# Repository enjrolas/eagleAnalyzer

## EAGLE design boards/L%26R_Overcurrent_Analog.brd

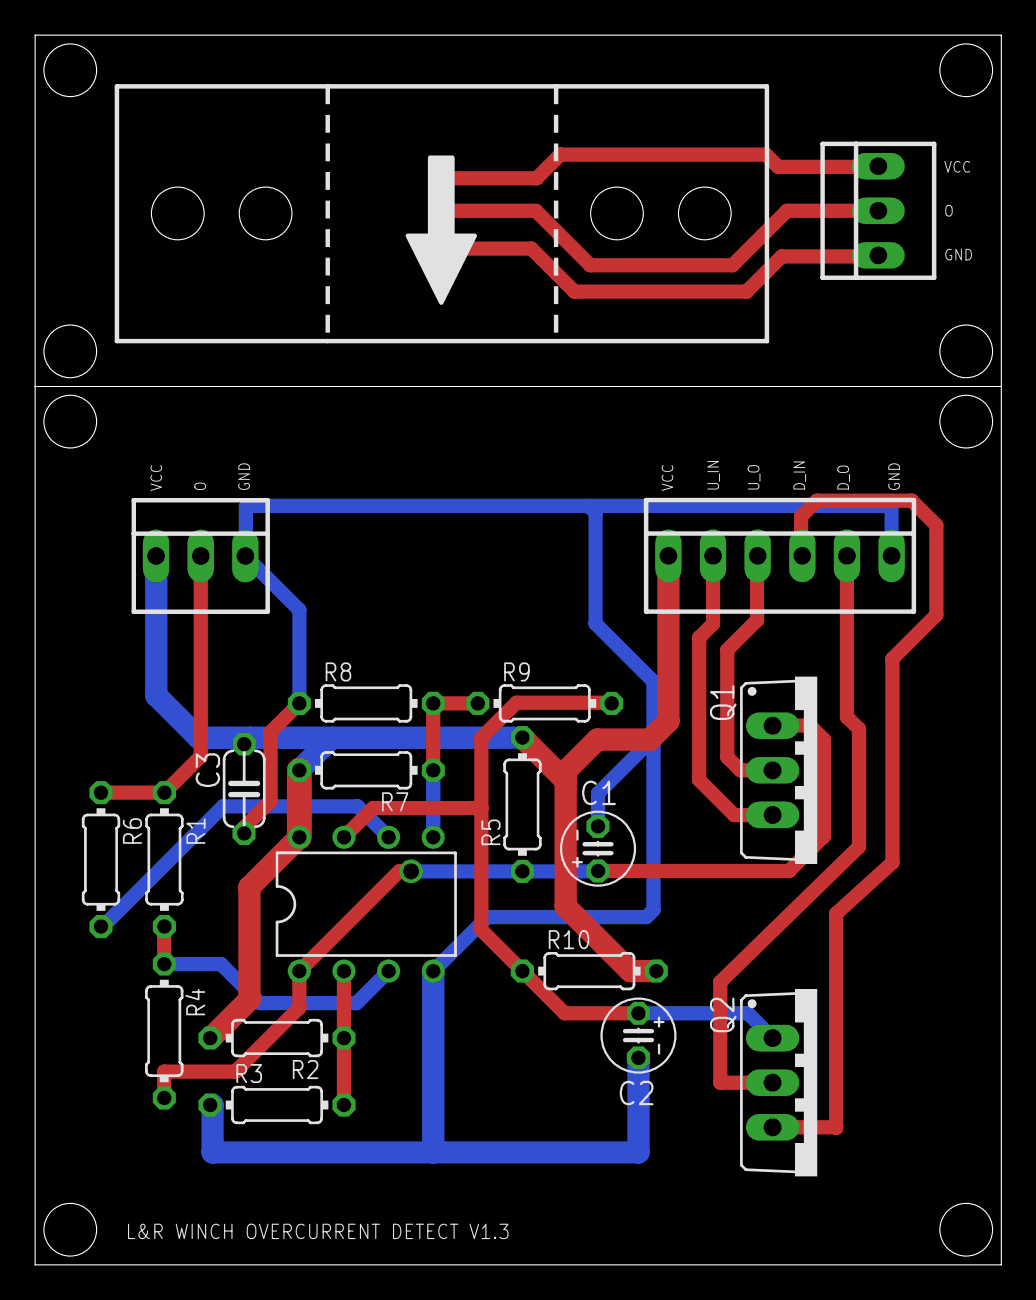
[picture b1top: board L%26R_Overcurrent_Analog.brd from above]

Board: 2 copper layers, 55.0 x 70.0 mm, 20 parts (0 on the bottom side), 16 nets.

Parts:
C1: 22u; C025-050X050
C2: 22u\; C025-050X050
C3: 0.1u; C050-024X044
IC1: CSLA2CFTH; CSLA2CF
IC2: TLC393CPN; DIL08
Q1, Q2: SUP75P0307; TO220BV
R1, R6: 3k; 0204/7
R2, R5, R10: 10k; 0204/7
R3: 24k; 0204/7
R4, R9: 1M; 0204/7
R7: 15k; 0204/7
R8: 6.2k; 0204/7
X1: J1; 22-23-2061
X2: J2; 22-23-2031
X3: J3; 22-23-2031

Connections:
+12V: C3.1, IC2.8, R2.2, R5.2, R7.2, R10.2, X1.1, X2.1
GND: C1.2, C2.2, C3.2, IC2.4, R3.1, R8.1, X1.6, X2.3
unnamed: IC2.3, R1.2, R4.1
unnamed: IC2.2, R2.1, R3.2
unnamed: IC2.6, R6.2
unnamed: IC2.5, R7.1, R8.2, R9.1
unnamed: C1.1, IC2.1, Q1.G, R4.2, R5.1
unnamed: C2.1, IC2.7, Q2.G, R9.2, R10.1
unnamed: Q1.S, X1.2
unnamed: Q1.D, X1.3
unnamed: Q2.S, X1.4
unnamed: Q2.D, X1.5
unnamed: IC1.V+, X3.1
unnamed: IC1.V-, X3.3
unnamed: IC1.O, X3.2
unnamed: R1.1, R6.1, X2.2

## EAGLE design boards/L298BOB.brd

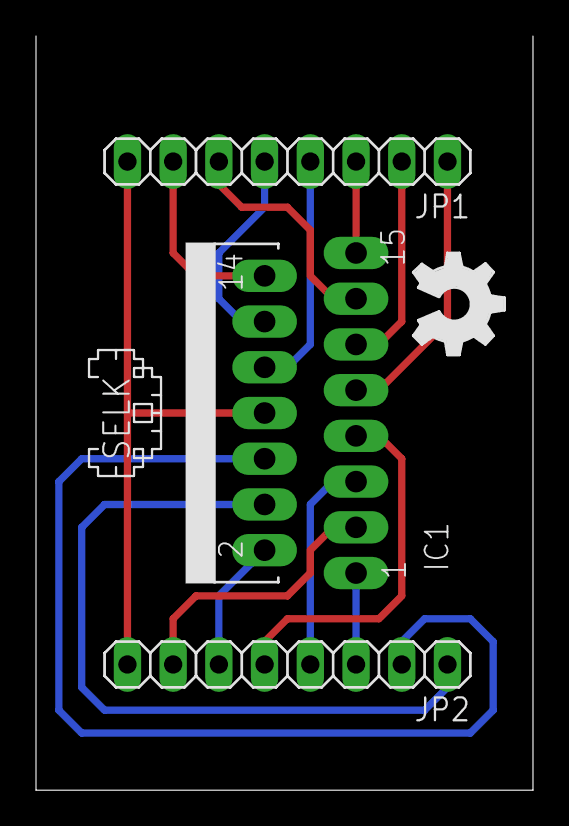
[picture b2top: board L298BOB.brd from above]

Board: 2 copper layers, 27.6 x 41.9 mm, 5 parts (0 on the bottom side), 15 nets.

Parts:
IC1: L298; MULTIWATT-15
JP1, JP2: 1X08
LOGO1: OSHW_LOGO_FILLX0200-NT; OSHW_FILLX200_NOTEXT
U$1: SELK02

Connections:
GND: IC1.8, JP1.8, JP2.8
unnamed: IC1.4, JP2.1
unnamed: IC1.1, JP2.3
unnamed: IC1.5, JP2.4
unnamed: IC1.7, JP2.5
unnamed: IC1.2, JP2.6
unnamed: IC1.3, JP2.7
unnamed: IC1.9, JP1.1
unnamed: IC1.6, JP2.2
unnamed: IC1.11, JP1.2
unnamed: IC1.15, JP1.3
unnamed: IC1.10, JP1.4
unnamed: IC1.12, JP1.5
unnamed: IC1.13, JP1.6
unnamed: IC1.14, JP1.7

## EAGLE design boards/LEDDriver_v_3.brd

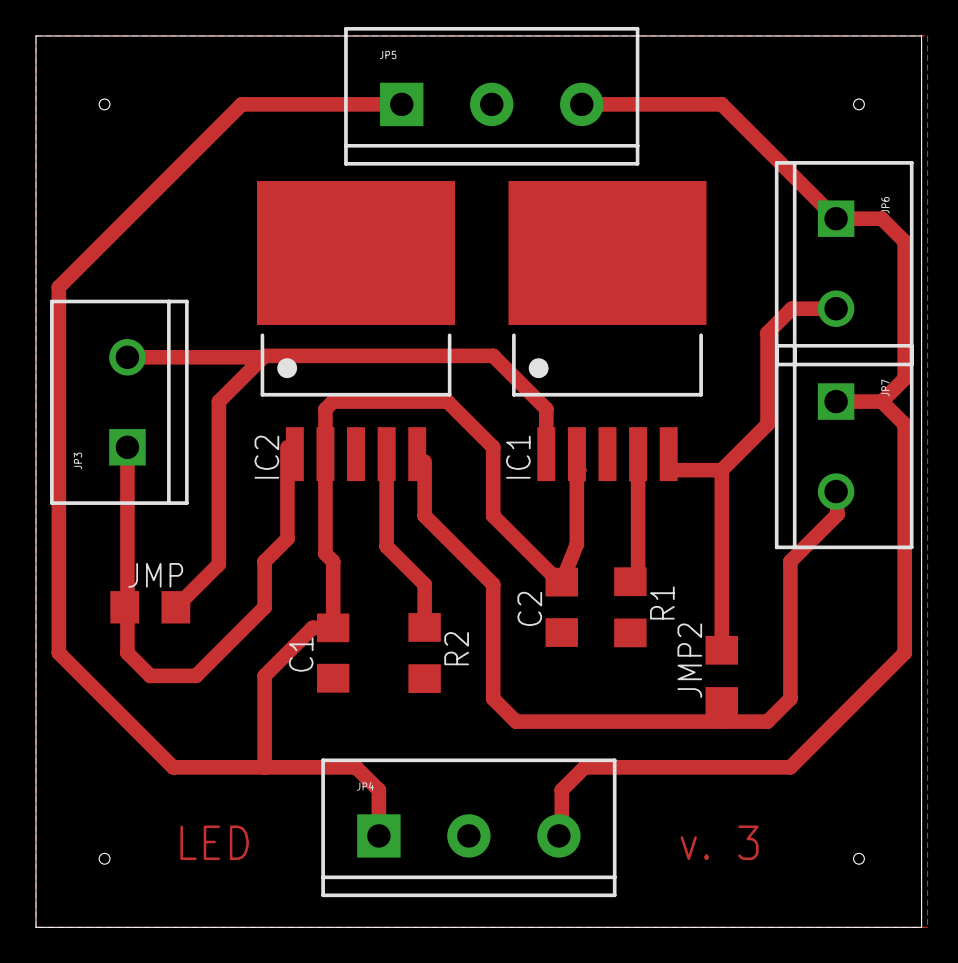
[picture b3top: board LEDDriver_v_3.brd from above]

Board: 2 copper layers, 49.2 x 49.5 mm, 13 parts (0 on the bottom side), 9 nets.

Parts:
C1, C2: C1206
IC1, IC2: CAT4101; TO263_5
JMP: CH; R1206
JMP2: AMP; R1206
JP3, JP6, JP7: M025MM; SCREWTERMINAL-5MM-2
JP4, JP5: SCREWTERMINAL-5MM-3
R1, R2: R1206

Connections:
+5V: C1.2, C2.2, IC1.2, IC2.2, JP4.1, JP5.1
+12V: JP4.3, JP5.3, JP6.1, JP7.1
GND: C1.1, C2.1, IC1.3, IC1.TAB, IC2.3, IC2.TAB, JP4.2, JP5.2, R1.2, R2.2
unnamed: IC1.1, JMP.2, JP3.2
unnamed: IC2.1, JMP.1, JP3.1
unnamed: IC1.4, R1.1
unnamed: IC2.5, JMP2.1, JP7.2
unnamed: IC1.5, JMP2.2, JP6.2
unnamed: IC2.4, R2.1

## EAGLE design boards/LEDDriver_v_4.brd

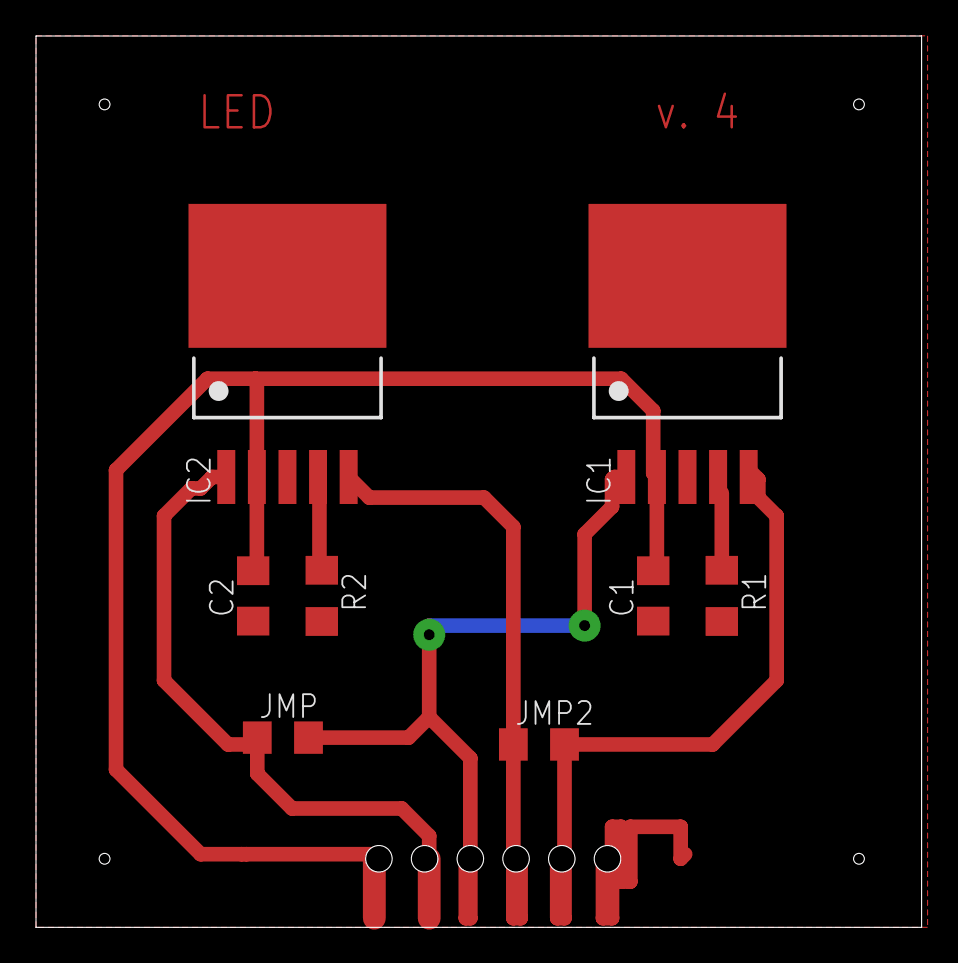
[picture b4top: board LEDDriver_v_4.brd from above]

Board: 2 copper layers, 49.2 x 49.5 mm, 9 parts (0 on the bottom side), 8 nets.

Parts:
C1, C2: C1206
IC1, IC2: CAT4101; TO263_5
JMP: CH; R1206
JMP2: AMP; R1206
JP1: 1X06_HOLES_ONLY
R1, R2: R1206

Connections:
+5V: C1.2, C2.2, IC1.2, IC2.2, JP1.6
GND: C1.1, C2.1, IC1.3, IC1.TAB, IC2.3, IC2.TAB, JP1.1, R1.2, R2.2
unnamed: IC1.1, JMP.2, JP1.4
unnamed: IC2.1, JMP.1, JP1.5
unnamed: IC1.4, R1.1
unnamed: IC2.5, JMP2.1, JP1.3
unnamed: IC1.5, JMP2.2, JP1.2
unnamed: IC2.4, R2.1

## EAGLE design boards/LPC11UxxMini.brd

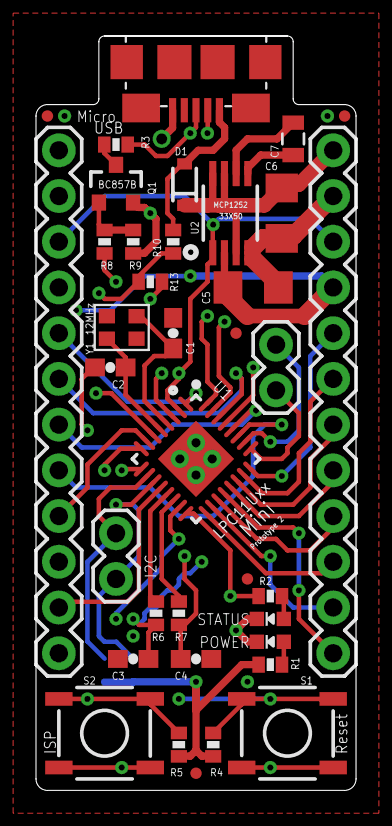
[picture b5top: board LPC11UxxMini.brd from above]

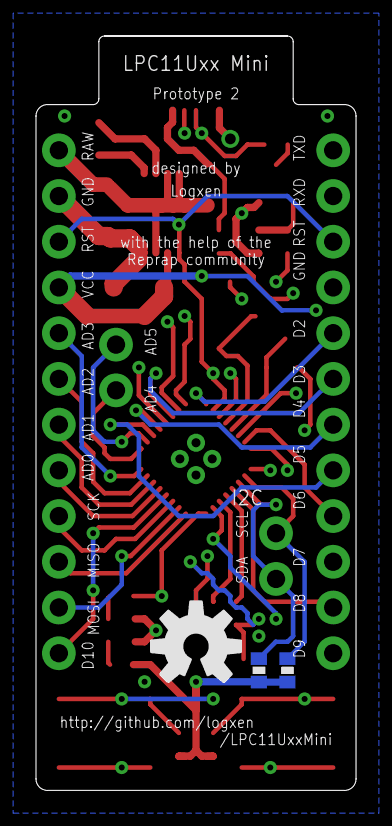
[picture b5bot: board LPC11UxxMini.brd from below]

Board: 4 copper layers, 17.8 x 41.9 mm, 40 parts (3 on the bottom side), 42 nets.

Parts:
C1, C2, C3, C4: 18pF; 0603-CAP
C5, C6: 10uF; 1206
C7: 1uF; 0805
D1: B0540WS-7; SOD-323
JP1, JP2: M12PTH; 1X12
JP3, JP6, JP7, JP8, JP9: FIDUCIALUFIDUCIAL; MICRO-FIDUCIAL
JP4: I2C; 1X02
JP5: ADC; 1X02
POWER: 20mA; CHIPLED_0603_NOOUTLINE
Q1: BC857B; SOT23-3
R1: 330 Ohm; 0402-RES
R2: 200 Ohm; 0402-RES
R3: 1.5kOhm; 0402-RES
R4, R5, R11, R12, R13: 10kOhm; 0402-RES
R6, R7: 33 Ohm; 0402-RES
R8: 3kOhm; 0402-RES
R9: 24kOhm; 0402-RES
R10: 100 Ohm; 0402-RES
S1: Reset; TACTILE_SWITCH_SMD
S2: ISP; TACTILE_SWITCH_SMD
STATUS: 20mA; CHIPLED_0603_NOOUTLINE
U1: LPC11Uxx; HVQFN32-5X5_3MMTHERMAL
U2: MCP1252-33X50I/MS; MSOP8_0.65MM
U$1: USB-MICROB-SMDRECEPT; USB-MICROB-RECEPT
U$4: OSHW-LOGO-M
Y1: 12MHz; CRYSTAL_2.5X2

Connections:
AD0: JP2.5, U1.21
AD1: JP2.6, U1.22
AD2: JP2.7, U1.23
AD3: JP2.8, U1.24
AD4: JP5.1, U1.25
AD5: JP5.2, U1.26
D2: JP1.5, U1.1
D3: JP1.6, U1.30
D4: JP1.7, U1.28
D5: JP1.8, U1.27
D6: JP1.9, U1.7
D7: JP1.10, U1.8
D8: JP1.11, U1.12
D9: JP1.12, R2.1, U1.16
D10: JP2.1, U1.20
GND: C1.2, C2.2, C3.2, C4.2, C5.2, C6.2, JP1.4, JP2.11, POWER.C, R13.1, S1.1, S1.2, S2.1, S2.2, STATUS.C, U1.THERMAL, U1.THERMAL@1, U1.THERMAL@2, U1.THERMAL@3, U1.THERMAL@4, U2.4, U$1.5
ISP: R5.1, S2.3, S2.4, U1.3
MC_USB_DM: R6.2, U1.13
MC_USB_DP: R7.2, U1.14
MC_USB_VBUS: R10.2, R13.2, U1.9
MISO: JP2.3, U1.17
MOSI: JP2.2, U1.18
POWER_LED_RESISTOR: POWER.A, R1.2
PWRREG_C+: C7.1, U2.6
PWRREG_C-: C7.2, U2.5
RST: JP1.3, JP2.10, R4.1, S1.3, S1.4, U1.2, U2.1
RXD: JP1.2, U1.31
SCK: JP2.4, U1.19
SCL: JP4.2, R11.1, U1.10
SDA: JP4.1, R12.1, U1.11
STATUS_LED_RESISTOR: R2.2, STATUS.A
TXD: JP1.1, U1.32
USB_CONNECT: R8.1, U1.15
USB_CONNECT_BASE: Q1.1, R8.2, R9.1
USB_CONNECT_COLLECTOR: Q1.3, R3.1
USB_DM: C3.1, R6.1, U$1.2
USB_DP: C4.1, R3.2, R7.1, U$1.3
USB_VBUS: D1.2, R10.1, U$1.1
VCC: C5.1, JP2.9, Q1.2, R1.1, R4.2, R5.2, R9.2, R11.2, R12.2, U1.6, U1.29, U2.2
VIN: C6.1, D1.1, JP2.12, U2.3, U2.7, U2.8
XTALIN: C1.1, U1.4, Y1.1
XTALOUT: C2.1, U1.5, Y1.3

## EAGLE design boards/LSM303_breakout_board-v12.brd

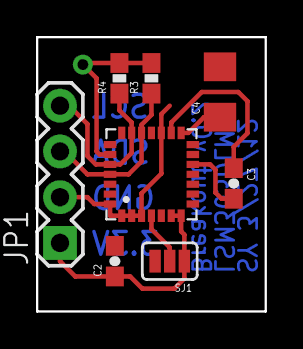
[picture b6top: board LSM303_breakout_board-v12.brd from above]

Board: 2 copper layers, 12.7 x 15.2 mm, 9 parts (0 on the bottom side), 8 nets.

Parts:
C2: 0.1uF; 0603-CAP
C3: 0.22uF; 0603-CAP
C4: 4.7uF; 1206
JP1: 1X04
R3, R4: 4.7k; 0603-RES
SJ1: SJ_3_PASTE2&3
U1: LSM303DLHSMD; LGA28-5X5
U$5: CREATIVE_COMMONS

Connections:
3.3V: C2.1, JP1.1, R3.2, R4.2, SJ1.1, U1.6, U1.7, U1.23
unnamed: C2.2, C4.2, JP1.2, SJ1.3, U1.1, U1.2, U1.3, U1.17, U1.28
unnamed: C3.1, U1.16
unnamed: C3.2, U1.12
unnamed: C4.1, U1.15
SA0_A: SJ1.2, U1.4
SCL: JP1.4, R4.1, U1.20, U1.24
SDA: JP1.3, R3.1, U1.19, U1.25

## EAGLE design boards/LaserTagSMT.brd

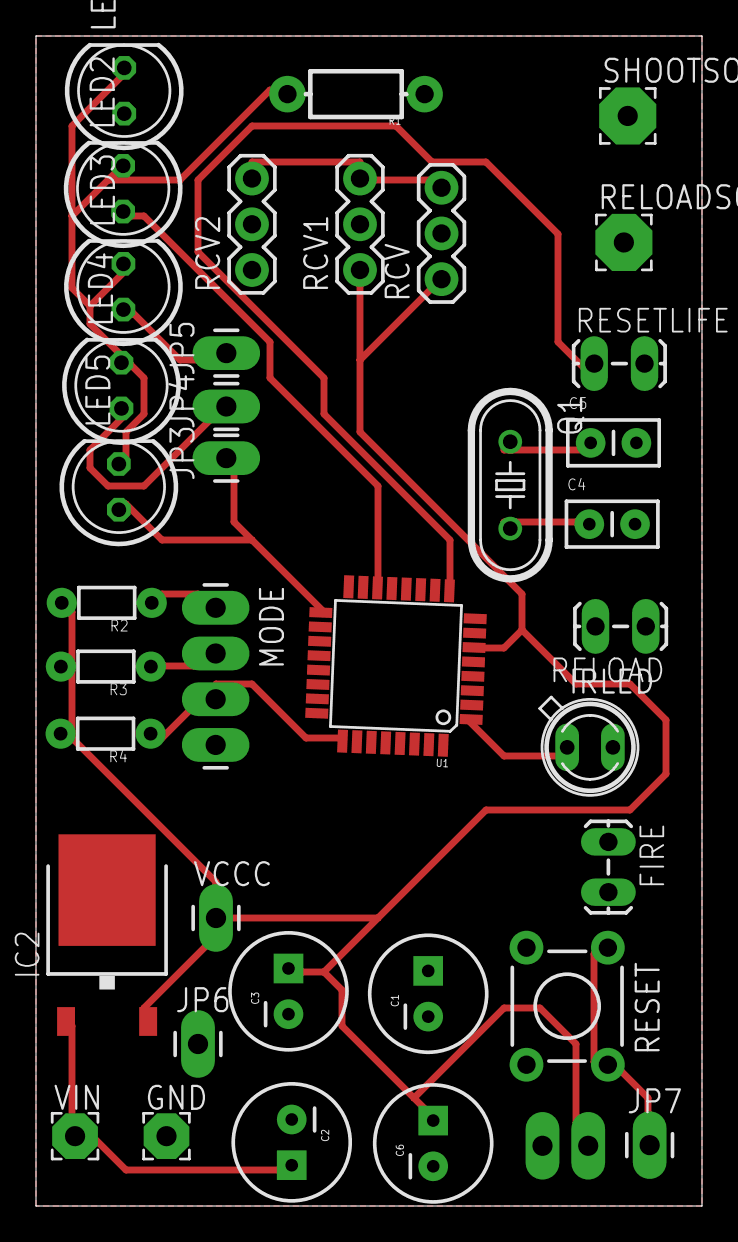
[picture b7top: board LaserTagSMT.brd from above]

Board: 2 copper layers, 37.0 x 65.0 mm, 38 parts (0 on the bottom side), 23 nets.

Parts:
C1, C2, C3, C6: CPOL-RADIAL-100UF-25V
C4, C5: CAP-PTH-SMALLEZ
FIRE: 1X02_LOCK_LONGPADS
GND: GND PAD; 2,54/1,1
IC2: 7805DT; TO252
IRLED: SFH482
JP3: 13; 1X01_LONGPAD
JP4: 12; 1X01_LONGPAD
JP5: 11; 1X01_LONGPAD
JP6, JP7: M01PTH_LONGPAD; 1X01_LONGPAD
LED1, LED2, LED3, LED4, LED5: LED5MM
MODE: 1X04_LONGPADS
Q1: HC49/S
R1: AXIAL-0.3-KIT
R2, R3, R4: 1/6W-RES
RCV, RCV1, RCV2: IR RCVR; 1X03
RELOAD: 1X02_LOCK_LONGPADS
RELOADSOUND: RELOAD; 3,17/1,1
RESET: TACTILE-PTH
RESETLIFE: 1X02_LOCK_LONGPADS
SHOOTSOUND: SHOOT; 3,17/1,1
U1: ATMEGA168; TQFP32-08
VCCC: 5; 1X01_LONGPAD
VIN: Vin PAD; 2,54/1,1
VOUT: 1X02_LONGPADS

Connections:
CONNECT: FIRE.1, U1.32
GND: C1.2, C2.2, C3.2, C4.2, C5.2, C6.2, FIRE.2, GND.1, IC2.3, IRLED.K, JP6.1, MODE.4, R1.P$1, RCV.2, RCV1.2, RCV2.2, RELOAD.2, RESET.3, RESET.4, RESETLIFE.2, U1.3, U1.5, U1.21, VOUT.2
IR_RCV: RCV.3, RCV1.3, RCV2.3, U1.10
unnamed: C2.1, IC2.1, VIN.1
unnamed: C1.1, U1.20
unnamed: LED1.A, U1.13
unnamed: C5.1, Q1.1, U1.8
unnamed: LED2.A, U1.14
unnamed: C4.1, Q1.2, U1.7
unnamed: JP5.1, LED3.A, U1.15
unnamed: JP4.1, LED4.A, U1.16
unnamed: JP3.1, LED5.A, U1.17
unnamed: LED1.K, LED2.K, LED3.K, LED4.K, LED5.K, R1.P$2
unnamed: IRLED.A, U1.1
unnamed: RELOAD.1, U1.2
unnamed: RESETLIFE.1, U1.9
unnamed: MODE.1, R2.1, U1.23
unnamed: MODE.2, R3.1, U1.24
unnamed: MODE.3, R4.1, U1.25
RELOADSOUND: RELOADSOUND.1, U1.12
RESETWIRE: JP7.1, RESET.1, RESET.2, U1.29
SHOOTSOUND: SHOOTSOUND.1, U1.11
VCC: C3.1, C6.1, IC2.2, R2.2, R3.2, R4.2, RCV.1, RCV1.1, U1.4, U1.6, U1.18, VCCC.1, VOUT.1

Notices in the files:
boards/L298BOB.brd:
CC-BY-SA
parts and their libraries:
SparkFun-Connectors: Licensing: CC v3.0 Share-Alike You are welcome to use this library for commercial purposes.
microbuilder: This work is placed in the public domain, and may be freely used for commercial and non-commercial work with the following conditions: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
